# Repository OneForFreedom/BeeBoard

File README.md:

# BeeBoard
Bee themed snappy split buzzy keyboard!
I made this because I need to overcome my fear of bees.
It's a keyboard with a standard iso layout with 2 spacebars. 
It has magnets incase you want to use them as one.

## EYECANDY!

# Firmware

This keyboard uses kmk firmware to work. both keyboards will work together to provide an input. This code is using a key matrix system for both halves. Left side is Master and Right side is Slave. Code R.py flashes to the right side and Code L.py flashes to the left.
the split keeb is wireless so it uses bluetooth to connect to each half and to your computer. The codes can be found here [here](/Firmware)

## BeeBoard BOM

| Name               | Price (£) | Price ($) | Link                                                                                     |
|--------------------|-----------|-----------|------------------------------------------------------------------------------------------|
| Nano Chip          | 2.25      | 3.06      | [Link](https://www.aliexpress.com/item/1005007040333351.html)                            |
| Switches           | 21.39     | 29.08     | [Link](https://www.aliexpress.com/item/1005008760267631.html)                            |
| Switch Film        | 2.00      | 2.72      | [Link](https://www.aliexpress.com/item/1005006584258877.html)                            |
| Diodes             | 1.40      | 1.90      | [Link](https://www.aliexpress.com/item/1005006245109375.html)                            |
| Stabilizers         | 9.29      | 12.63     | [Link](https://www.aliexpress.com/item/32719735398.html)                            |
| O Rings            | 0.57      | 0.78      | [Link](https://www.aliexpress.com/item/32965363255.html)                                 |
| Super Glue         | 2.12      | 2.88      | [Link](https://www.aliexpress.com/item/1005008583356354.html)                            |
| Magnets            | 5.15      | 7.00      | [Link](https://www.aliexpress.com/item/1005008882082220.html)                            |
| Switch Felts       | 2.52      | 3.43      | [Link](https://www.aliexpress.com/item/1005006454684461.html)                            |
| Batteries          | 12.78     | 17.37     | [Link](https://www.amazon.co.uk/gp/product/B0C7462TMS)                                    |
| 3D Printing & Shipping | 5.00  | 6.80      | [Link](https://send.royalmail.com/send/youritem?country=GBR&format&weight=&weightUnit=G)  |
| PCB                | 33.58     | 45.63     | [Link](https://jlcpcb.com/)                                                              |
| Chargers (x2)      | 1.70      | 2.31      | [Link](https://www.aliexpress.com/item/1005007504310983.html)                            |
| Keycaps            | 6.28      | 8.53      | [Link](https://www.aliexpress.com/item/1005008144804720.html)                            |

---

### Grand Totals:

| Currency | Total    |
|----------|----------|
| GBP      | £105.79  |
| USD      | $143.09  |

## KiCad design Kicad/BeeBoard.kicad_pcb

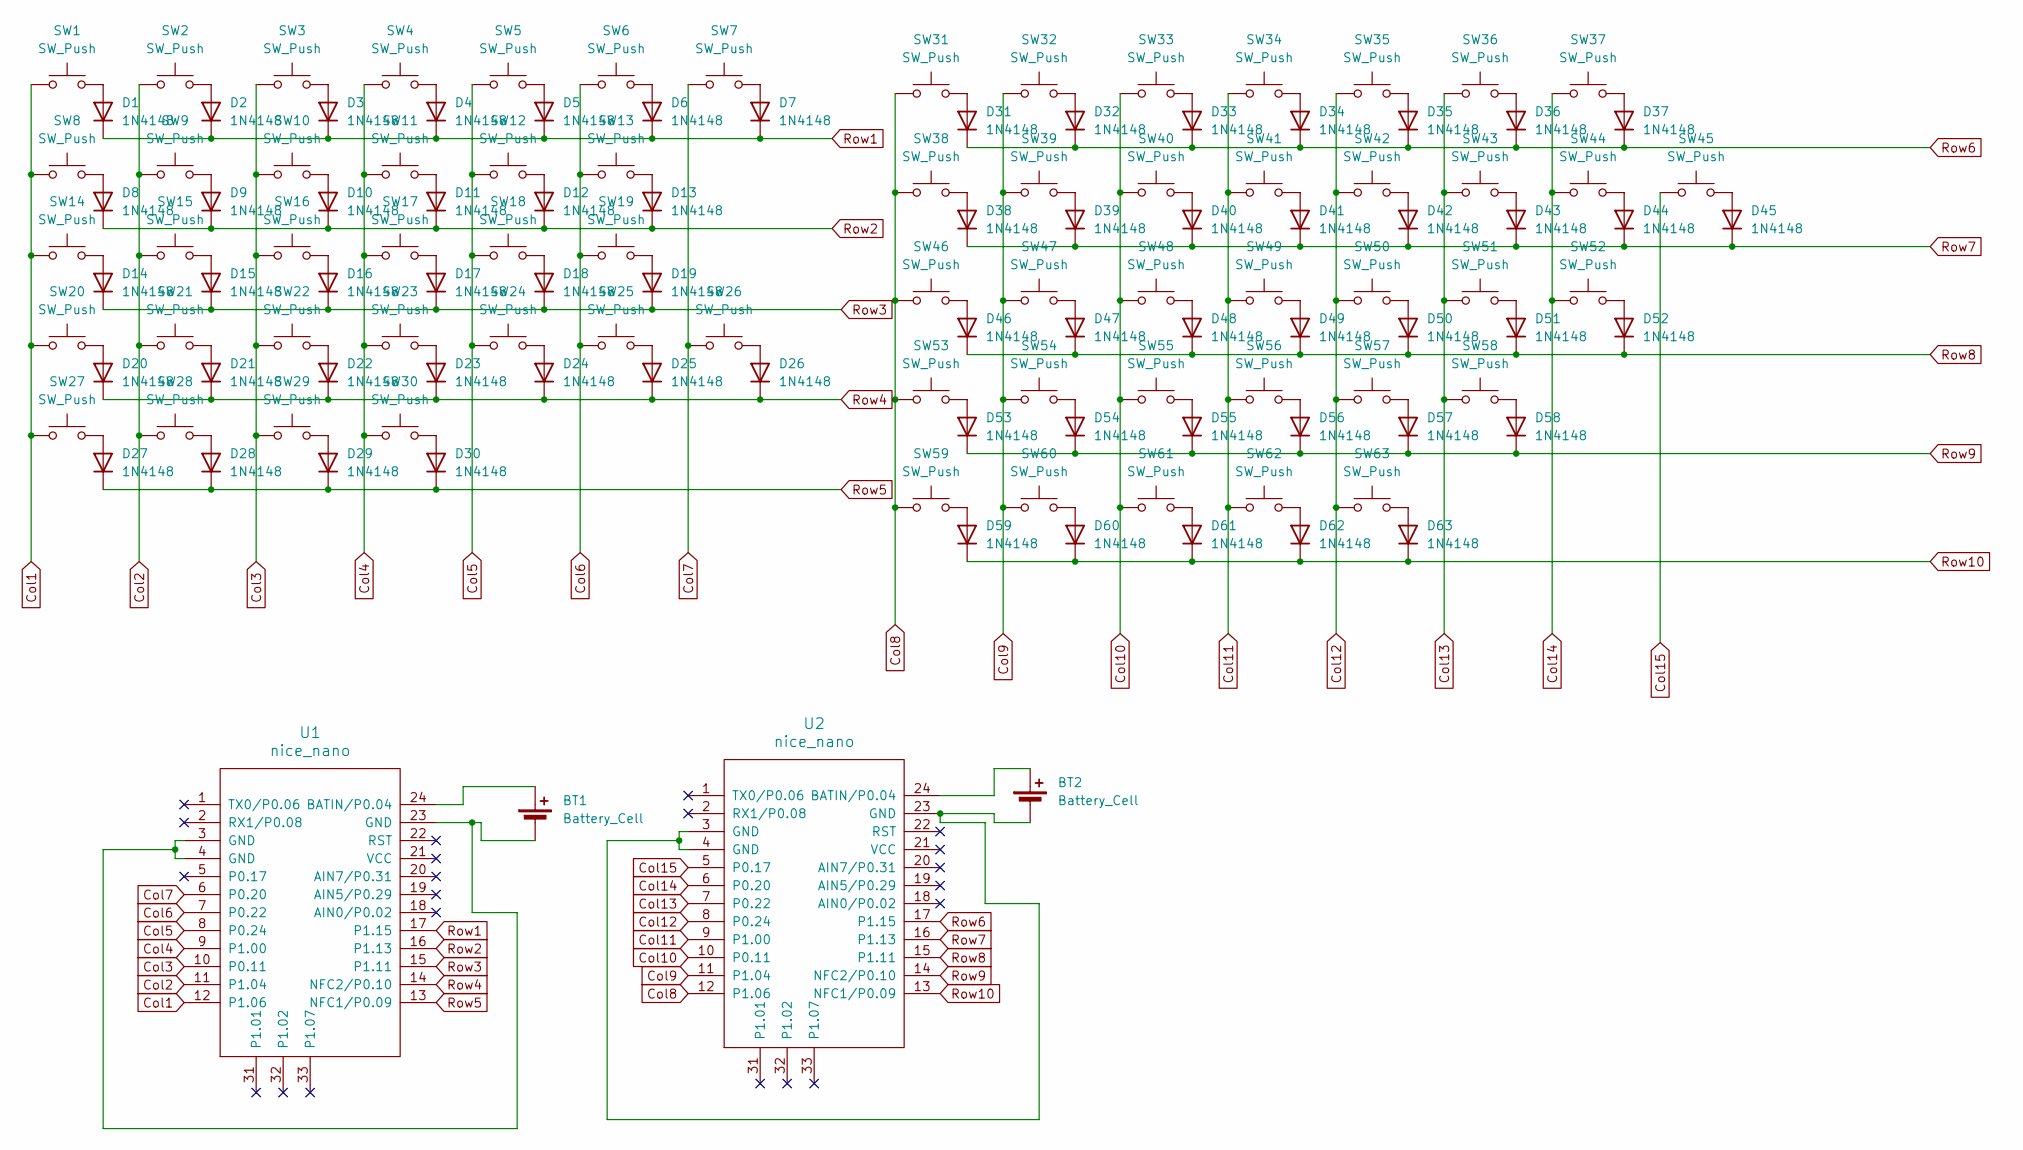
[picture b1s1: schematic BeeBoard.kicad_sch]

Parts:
BT1, BT2: Battery_Cell
D1, D2, D3, D4, D5, D6, D7, D8, D9, D10, D11, D12, D13, D14, D15, D16, D17, D18, D19, D20, D21, D22, D23, D24, D25, D26, D27, D28, D29, D30, D31, D32, D33, D34, D35, D36, D37, D38, D39, D40, D41, D42, D43, D44, D45, D46, D47, D48, D49, D50, D51, D52, D53, D54, D55, D56, D57, D58, D59, D60, D61, D62, D63: 1N4148; D_DO-35_SOD27_P7.62mm_Horizontal
SW1, SW2, SW3, SW4, SW5, SW6, SW7, SW8, SW9, SW10, SW11, SW12, SW13, SW14, SW15, SW16, SW17, SW18, SW19, SW20, SW21, SW22, SW23, SW24, SW25, SW26, SW27, SW28, SW29, SW30, SW31, SW32, SW33, SW34, SW35, SW36, SW37, SW38, SW39, SW40, SW41, SW42, SW43, SW44, SW45, SW46, SW47, SW48, SW49, SW50, SW51, SW52, SW53, SW54, SW55, SW56, SW57, SW58, SW59, SW60, SW61, SW62, SW63: SW_Push; SW_Cherry_MX_1.00u_PCB
U1, U2: nice_nano

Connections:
Col1: SW1.1, SW8.1, SW14.1, SW20.1, SW27.1, U1.12 (P1.06)
Col2: SW2.1, SW9.1, SW15.1, SW21.1, SW28.1, U1.11 (P1.04)
Col3: SW3.1, SW10.1, SW16.1, SW22.1, SW29.1, U1.10 (P0.11)
Col4: SW4.1, SW11.1, SW17.1, SW23.1, SW30.1, U1.9 (P1.00)
Col5: SW5.1, SW12.1, SW18.1, SW24.1, U1.8 (P0.24)
Col6: SW6.1, SW13.1, SW19.1, SW25.1, U1.7 (P0.22)
Col7: SW7.1, SW26.1, U1.6 (P0.20)
Col8: SW31.1, SW38.1, SW46.1, SW53.1, SW59.1, U2.12 (P1.06)
Col9: SW32.1, SW39.1, SW47.1, SW54.1, SW60.1, U2.11 (P1.04)
Col10: SW33.1, SW40.1, SW48.1, SW55.1, SW61.1, U2.10 (P0.11)
Col11: SW34.1, SW41.1, SW49.1, SW56.1, SW62.1, U2.9 (P1.00)
Col12: SW35.1, SW42.1, SW50.1, SW57.1, SW63.1, U2.8 (P0.24)
Col13: SW36.1, SW43.1, SW51.1, SW58.1, U2.7 (P0.22)
Col14: SW37.1, SW44.1, SW52.1, U2.6 (P0.20)
Col15: SW45.1, U2.5 (P0.17)
unnamed: BT1.1 (+), U1.24 (BATIN/P0.04)
unnamed: BT1.2 (-), U1.3 (GND), U1.4 (GND), U1.23 (GND)
unnamed: BT2.1 (+), U2.24 (BATIN/P0.04)
unnamed: BT2.2 (-), U2.3 (GND), U2.4 (GND), U2.23 (GND)
unnamed: D1.2 (A), SW1.2
unnamed: D2.2 (A), SW2.2
unnamed: D3.2 (A), SW3.2
unnamed: D4.2 (A), SW4.2
unnamed: D5.2 (A), SW5.2
unnamed: D6.2 (A), SW6.2
unnamed: D7.2 (A), SW7.2
unnamed: D8.2 (A), SW8.2
unnamed: D9.2 (A), SW9.2
unnamed: D10.2 (A), SW10.2
unnamed: D11.2 (A), SW11.2
unnamed: D12.2 (A), SW12.2
unnamed: D13.2 (A), SW13.2
unnamed: D14.2 (A), SW14.2
unnamed: D15.2 (A), SW15.2
unnamed: D16.2 (A), SW16.2
unnamed: D17.2 (A), SW17.2
unnamed: D18.2 (A), SW18.2
unnamed: D19.2 (A), SW19.2
unnamed: D20.2 (A), SW20.2
unnamed: D21.2 (A), SW21.2
unnamed: D22.2 (A), SW22.2
unnamed: D23.2 (A), SW23.2
unnamed: D24.2 (A), SW24.2
unnamed: D25.2 (A), SW25.2
unnamed: D26.2 (A), SW26.2
unnamed: D27.2 (A), SW27.2
unnamed: D28.2 (A), SW28.2
unnamed: D29.2 (A), SW29.2
unnamed: D30.2 (A), SW30.2
unnamed: D31.2 (A), SW31.2
unnamed: D32.2 (A), SW32.2
unnamed: D33.2 (A), SW33.2
unnamed: D34.2 (A), SW34.2
unnamed: D35.2 (A), SW35.2
unnamed: D36.2 (A), SW36.2
unnamed: D37.2 (A), SW37.2
unnamed: D38.2 (A), SW38.2
unnamed: D39.2 (A), SW39.2
unnamed: D40.2 (A), SW40.2
unnamed: D41.2 (A), SW41.2
unnamed: D42.2 (A), SW42.2
unnamed: D43.2 (A), SW43.2
unnamed: D44.2 (A), SW44.2
unnamed: D45.2 (A), SW45.2
unnamed: D46.2 (A), SW46.2
unnamed: D47.2 (A), SW47.2
unnamed: D48.2 (A), SW48.2
unnamed: D49.2 (A), SW49.2
unnamed: D50.2 (A), SW50.2
unnamed: D51.2 (A), SW51.2
unnamed: D52.2 (A), SW52.2
unnamed: D53.2 (A), SW53.2
unnamed: D54.2 (A), SW54.2
unnamed: D55.2 (A), SW55.2
unnamed: D56.2 (A), SW56.2
unnamed: D57.2 (A), SW57.2
unnamed: D58.2 (A), SW58.2
unnamed: D59.2 (A), SW59.2
unnamed: D60.2 (A), SW60.2
unnamed: D61.2 (A), SW61.2
unnamed: D62.2 (A), SW62.2
unnamed: D63.2 (A), SW63.2
Row1: D1.1 (K), D2.1 (K), D3.1 (K), D4.1 (K), D5.1 (K), D6.1 (K), D7.1 (K), U1.17 (P1.15)
Row2: D8.1 (K), D9.1 (K), D10.1 (K), D11.1 (K), D12.1 (K), D13.1 (K), U1.16 (P1.13)
Row3: D14.1 (K), D15.1 (K), D16.1 (K), D17.1 (K), D18.1 (K), D19.1 (K), U1.15 (P1.11)
Row4: D20.1 (K), D21.1 (K), D22.1 (K), D23.1 (K), D24.1 (K), D25.1 (K), D26.1 (K), U1.14 (NFC2/P0.10)
Row5: D27.1 (K), D28.1 (K), D29.1 (K), D30.1 (K), U1.13 (NFC1/P0.09)
Row6: D31.1 (K), D32.1 (K), D33.1 (K), D34.1 (K), D35.1 (K), D36.1 (K), D37.1 (K), U2.17 (P1.15)
Row7: D38.1 (K), D39.1 (K), D40.1 (K), D41.1 (K), D42.1 (K), D43.1 (K), D44.1 (K), D45.1 (K), U2.16 (P1.13)
Row8: D46.1 (K), D47.1 (K), D48.1 (K), D49.1 (K), D50.1 (K), D51.1 (K), D52.1 (K), U2.15 (P1.11)
Row9: D53.1 (K), D54.1 (K), D55.1 (K), D56.1 (K), D57.1 (K), D58.1 (K), U2.14 (NFC2/P0.10)
Row10: D59.1 (K), D60.1 (K), D61.1 (K), D62.1 (K), D63.1 (K), U2.13 (NFC1/P0.09)

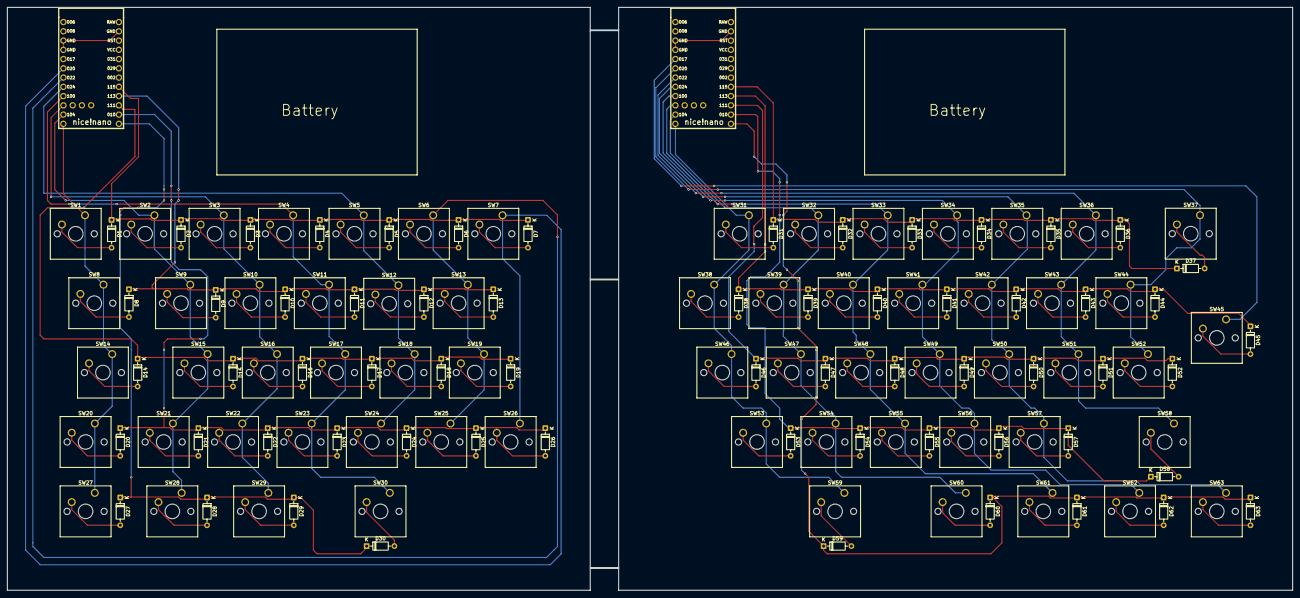
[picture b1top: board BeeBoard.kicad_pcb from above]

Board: 2 copper layers, 352.8 x 160.0 mm, 128 parts (0 on the bottom side), 90 nets.

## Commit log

2025-07-10 Rename BeeBoard NBG.png to Images/BeeBoard NBG.png
2025-07-10 Rename BeeBoard PCB.png to Images/BeeBoard PCB.png
2025-07-10 Rename BeeBoard.png to Images/BeeBoard.png
2025-07-10 Rename BeeBoard Schematic.png to Images/BeeBoard Schematic.png
2025-07-10 Rename BeeBoard.kicad_prl to Kicad/BeeBoard.kicad_prl
2025-07-10 Rename BeeBoard.kicad_pro to Kicad/BeeBoard.kicad_pro
2025-07-10 Rename BeeBoard.zip to Production/BeeBoard Gerbers.zip
2025-08-02 Rename codel.py to code L.py
2025-08-02 Rename coder.py to code R.py
